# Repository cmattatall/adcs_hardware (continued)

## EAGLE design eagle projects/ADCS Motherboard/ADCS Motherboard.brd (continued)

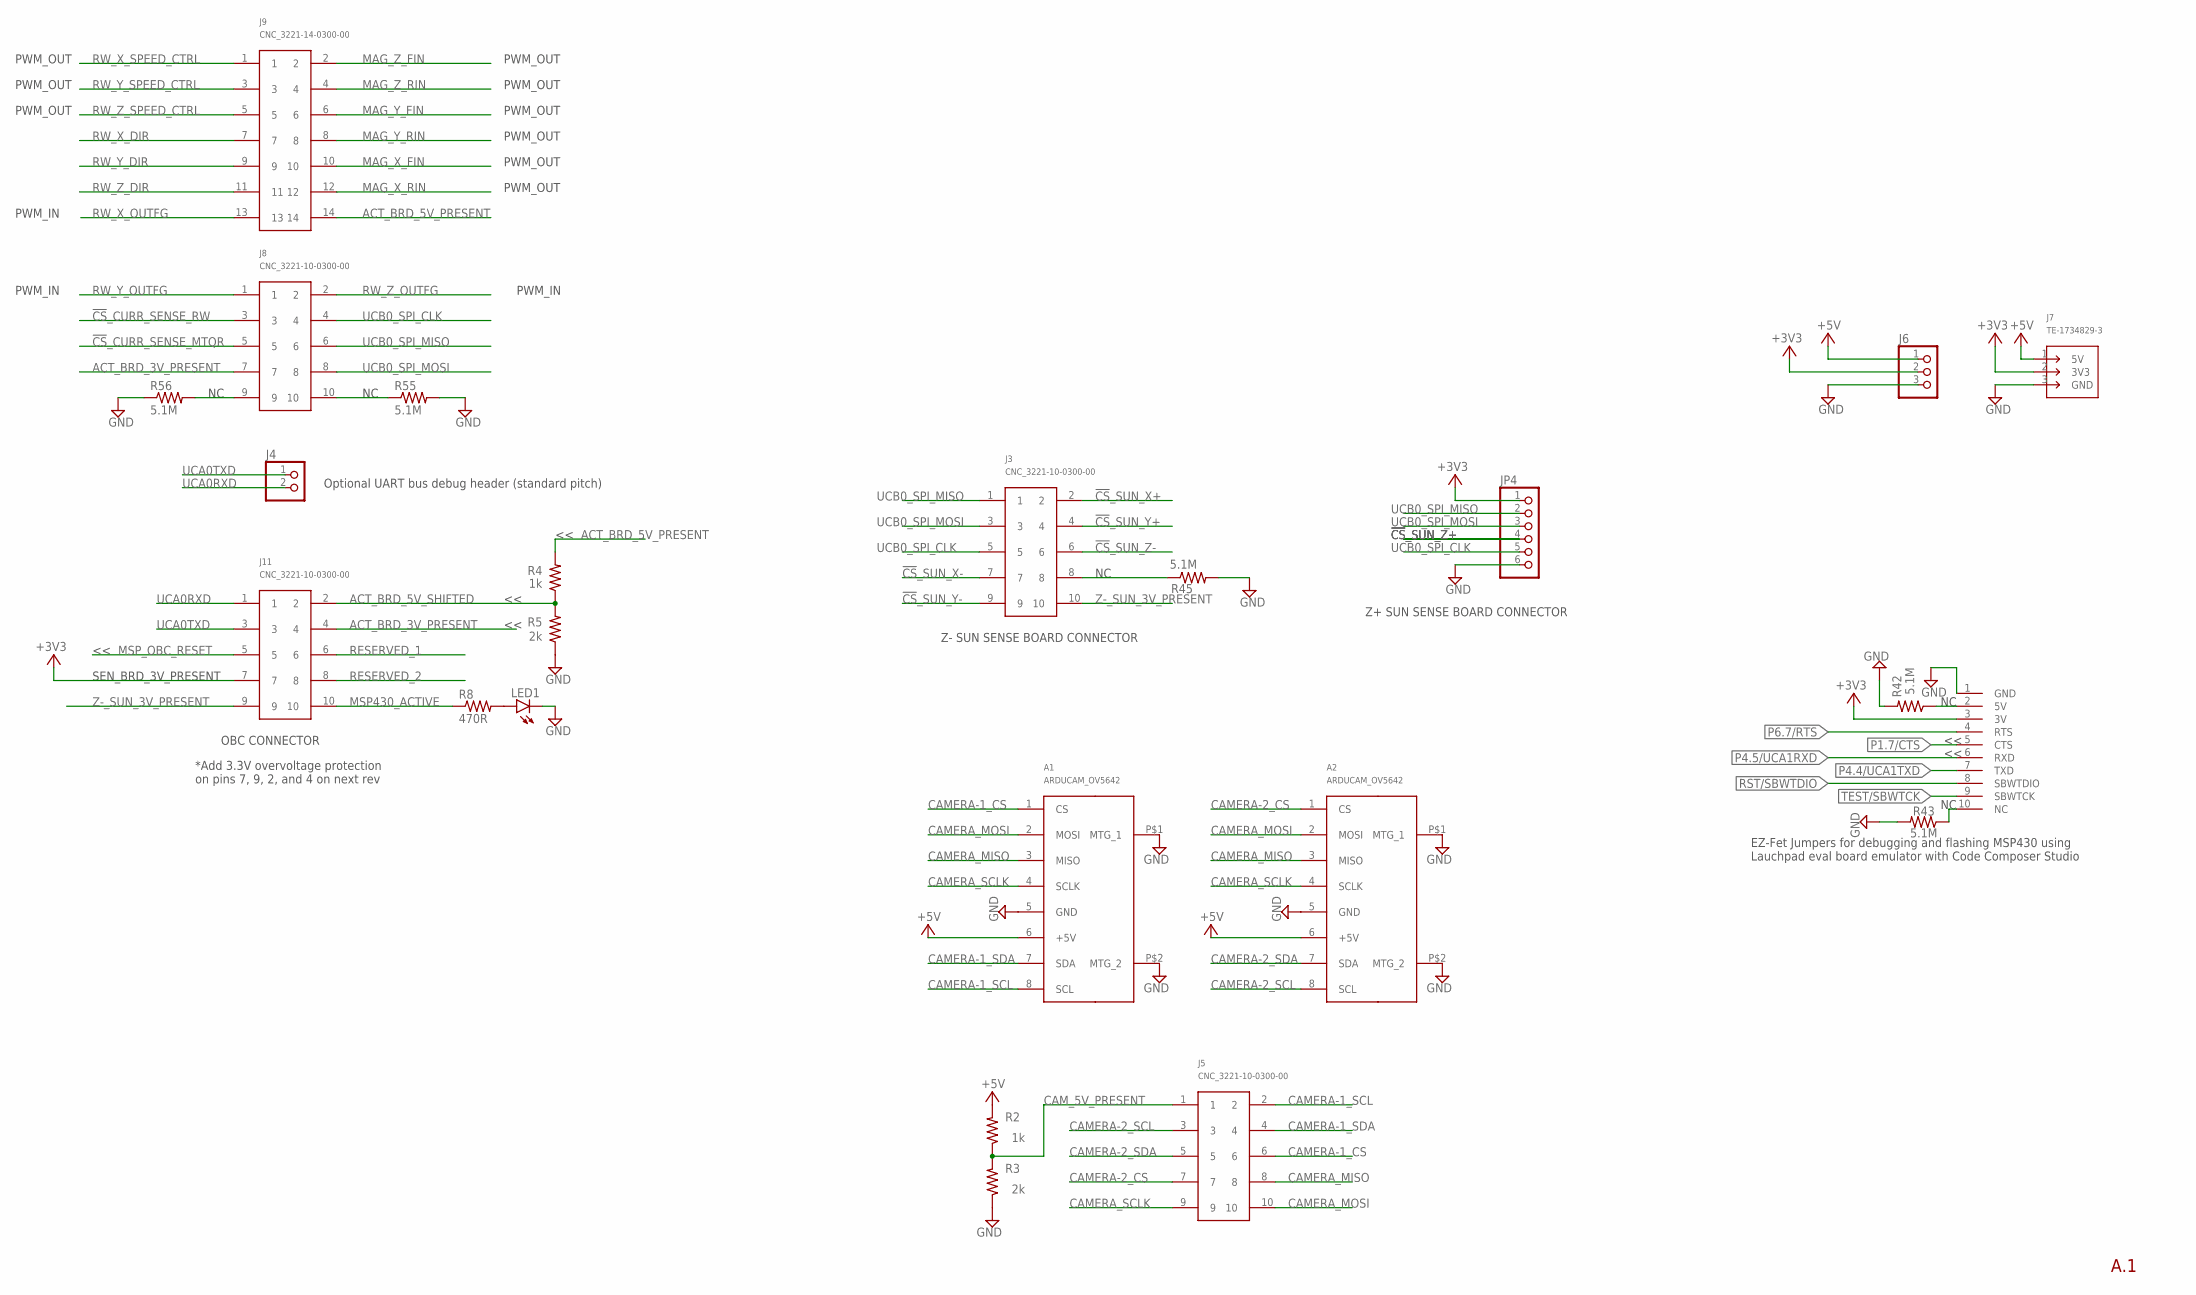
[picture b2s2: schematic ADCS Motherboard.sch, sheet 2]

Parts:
A1, A2: ARDUCAM_OV5642; ARDUCAM
J1: HDR_10_EZFET_DEBUGGER; HDRV10W66P254_10X1_2540X254H858
J3, J5, J8, J11: CNC_3221-10-0300-00
J4: HDR_1X2_; 1X02
J6: PINHD-1X3; 1X03
J7: TE-1734829-3
J9: CNC_3221-14-0300-00
JP4: PINHD-1X6; 1X06
LED1: LEDCHIP-LED0603; CHIP-LED0603
R2, R4: 1k; R0603
R3, R5: 2k; R0603
R8: 470R; R0603
R42, R43, R45: 5.1M; R0402
R55, R56: 5.1M; R0603

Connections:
!CS!_CURR_SENSE_MTQR: J8.5; also elsewhere on the board
!CS!_CURR_SENSE_RW: J8.3; also elsewhere on the board
!CS!_SUN_X+: J3.2; also elsewhere on the board
!CS!_SUN_X-: J3.7; also elsewhere on the board
!CS!_SUN_Y+: J3.4; also elsewhere on the board
!CS!_SUN_Y-: J3.9; also elsewhere on the board
!CS!_SUN_Z+: JP4.4; also elsewhere on the board
!CS!_SUN_Z-: J3.6; also elsewhere on the board
+3V3: J1.3 (3V), J6.2, J7.2 (3V3), J11.7, JP4.1; also elsewhere on the board
+5V: A1.6 (+5V), A2.6 (+5V), J6.1, J7.1 (5V), R2.2; also elsewhere on the board
ACT_BRD_3V_PRESENT: J8.7, J11.4
ACT_BRD_5V_PRESENT: J9.14, R4.2
ACT_BRD_5V_SHIFTED: J11.2, R4.1, R5.2
CAMERA-1_CS: A1.1 (CS), J5.6
CAMERA-1_SCL: A1.8 (SCL), J5.2
CAMERA-1_SDA: A1.7 (SDA), J5.4
CAMERA-2_CS: A2.1 (CS), J5.7
CAMERA-2_SCL: A2.8 (SCL), J5.3
CAMERA-2_SDA: A2.7 (SDA), J5.5
CAMERA_MISO: A1.3 (MISO), A2.3 (MISO), J5.8
CAMERA_MOSI: A1.2 (MOSI), A2.2 (MOSI), J5.10
CAMERA_SCLK: A1.4 (SCLK), A2.4 (SCLK), J5.9
CAM_5V_PRESENT: J5.1, R2.1, R3.2
GND: A1.5 (GND), A1.P$1 (MTG_1), A1.P$2 (MTG_2), A2.5 (GND), A2.P$1 (MTG_1), A2.P$2 (MTG_2), J1.1 (GND), J6.3, J7.3 (GND), JP4.6, LED1.C, R3.1, R5.1, R42.2, R43.2, R45.2, R55.2, R56.1; also elsewhere on the board
MAG_X_FIN: J9.10; also elsewhere on the board
MAG_X_RIN: J9.12; also elsewhere on the board
MAG_Y_FIN: J9.6; also elsewhere on the board
MAG_Y_RIN: J9.8; also elsewhere on the board
MAG_Z_FIN: J9.2; also elsewhere on the board
MAG_Z_RIN: J9.4; also elsewhere on the board
MSP430_ACTIVE: J11.10, R8.1; also elsewhere on the board
MSP_OBC_RESET: J11.5; also elsewhere on the board
unnamed: LED1.A, R8.2
unnamed: J1.2 (5V), R42.1
unnamed: J1.10 (NC), R43.1
unnamed: J8.9, R56.2
unnamed: J8.10, R55.1
unnamed: J3.8, R45.1
P1.7/CTS: J1.5 (CTS); also elsewhere on the board
P4.4/UCA1TXD: J1.7 (TXD); also elsewhere on the board
P4.5/UCA1RXD: J1.6 (RXD); also elsewhere on the board
P6.7/RTS: J1.4 (RTS); also elsewhere on the board
RESERVED_1: J11.6; also elsewhere on the board
RESERVED_2: J11.8; also elsewhere on the board
RST/SBWTDIO: J1.8 (SBWTDIO); also elsewhere on the board
RW_X_DIR: J9.7; also elsewhere on the board
RW_X_OUTFG: J9.13; also elsewhere on the board
RW_X_SPEED_CTRL: J9.1; also elsewhere on the board
RW_Y_DIR: J9.9; also elsewhere on the board
RW_Y_OUTFG: J8.1; also elsewhere on the board
RW_Y_SPEED_CTRL: J9.3; also elsewhere on the board
RW_Z_DIR: J9.11; also elsewhere on the board
RW_Z_OUTFG: J8.2; also elsewhere on the board
RW_Z_SPEED_CTRL: J9.5; also elsewhere on the board
TEST/SBWTCK: J1.9 (SBWTCK); also elsewhere on the board
UCA0RXD: J4.2, J11.1; also elsewhere on the board
UCA0TXD: J4.1, J11.3; also elsewhere on the board
UCB0_SPI_CLK: J3.5, J8.4, JP4.5; also elsewhere on the board
UCB0_SPI_MISO: J3.1, J8.6, JP4.2; also elsewhere on the board
UCB0_SPI_MOSI: J3.3, J8.8, JP4.3; also elsewhere on the board
Z-_SUN_3V_PRESENT: J3.10, J11.9

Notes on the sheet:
PWM_OUT
OBC CONNECTOR
SEN_BRD_3V_PRESENT
*Add 3.3V overvoltage protection on pins 7, 9, 2, and 4 on next rev
EZ-Fet Jumpers for debugging and flashing MSP430 using Lauchpad eval board emulator with Code Composer Studio
Optional UART bus debug header (standard pitch)
A.1
Z- SUN SENSE BOARD CONNECTOR
Z+ SUN SENSE BOARD CONNECTOR
PWM_IN

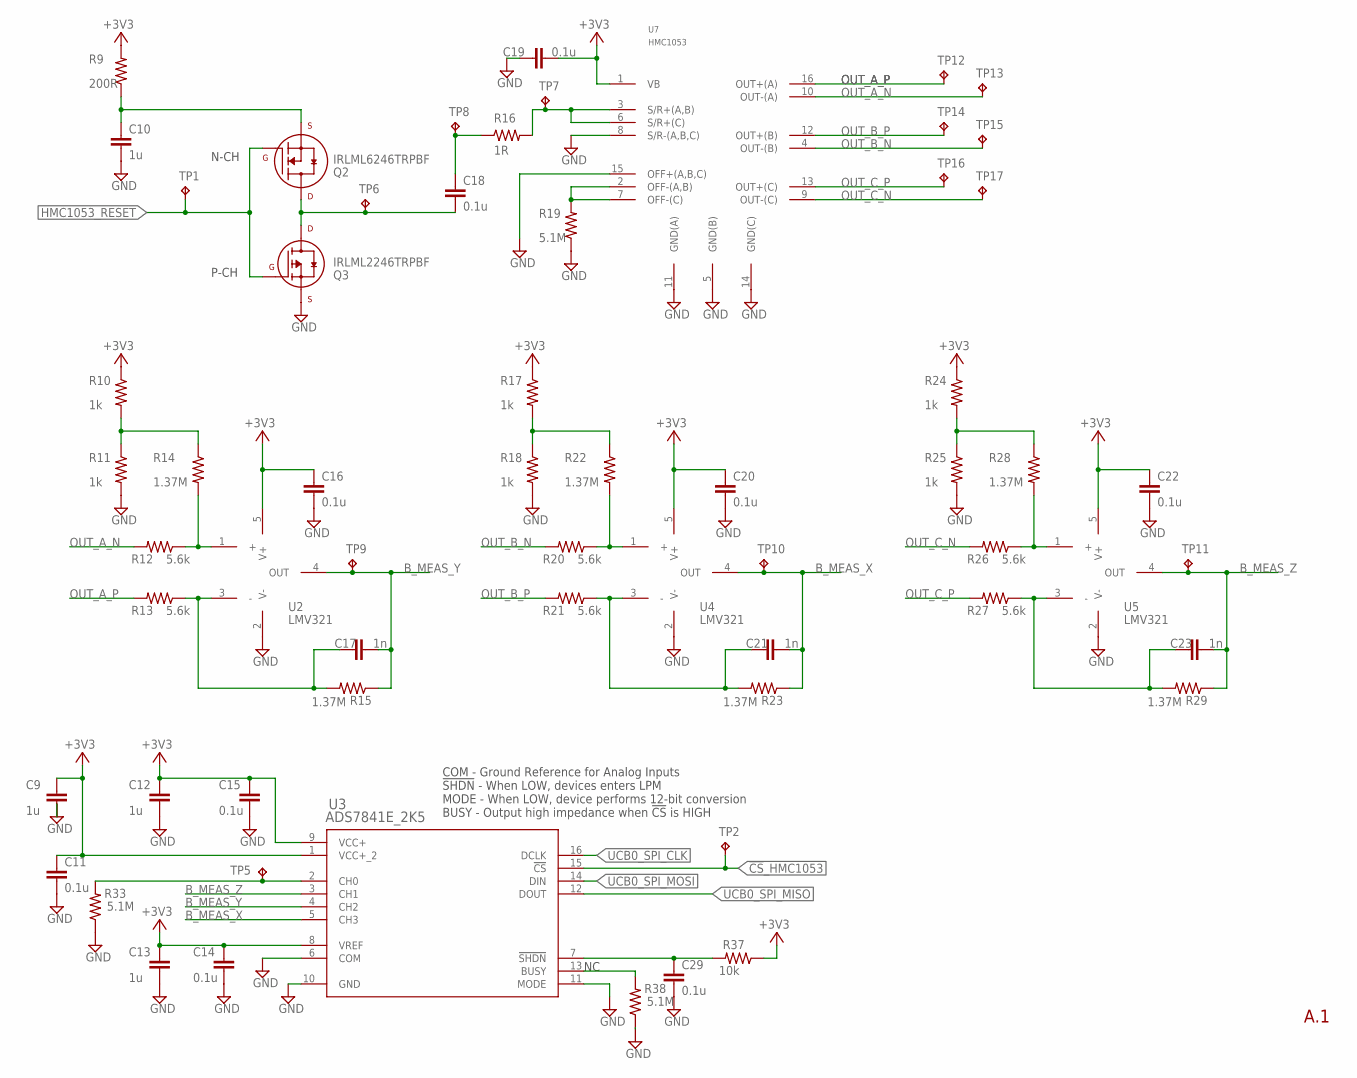
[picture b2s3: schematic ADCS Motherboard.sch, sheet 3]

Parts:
C9, C12, C13: 1u; C0805
C10: 1u; C0603
C11, C14, C15, C16, C19, C20, C22, C29: 0.1u; C0603
C17, C21, C23: 1n; C0603
C18: 0.1u; C0805
Q2: IRLML6246TRPBF; SOT23-3P95_237X112L25X40N_MICRO3
Q3: IRLML2246TRPBF; SOT23-3P95_237X112L25X40N_MICRO3
R9: 200R; R0805
R10, R11, R17, R18, R24, R25: 1k; R0603
R12, R13, R20, R21, R26, R27: 5.6k; R0603
R14, R15, R22, R23, R28, R29: 1.37M; R0603
R16: 1R; R0805
R19: 5.1M; R0805
R33, R38: 5.1M; R0402
R37: 10k; R0805
TP1, TP2, TP5, TP6, TP7, TP8, TP9, TP10, TP11, TP12, TP13, TP14, TP15, TP16, TP17: TESTPOINT; TP_P76H50
U2, U4, U5: LMV321; SC70-5P65_210X110L36X22N
U3: ADS7841E_2K5; DBQ16
U7: HMC1053; LCCS16P127_736X736X279L127X50N

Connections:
!CS!_HMC1053: TP2.1, U3.15 (!CS); also elsewhere on the board
+3V3: C9.1, C11.1, C12.1, C13.1, C14.1, C15.1, C16.1, C19.1, C20.1, C22.1, R9.2, R10.1, R17.1, R24.1, R37.1, U2.5 (V+), U3.1 (VCC+_2), U3.8 (VREF), U3.9 (VCC+), U4.5 (V+), U5.5 (V+), U7.1 (VB); also elsewhere on the board
B_MEAS_X: C21.2, R23.1, TP10.1, U3.5 (CH3), U4.4 (OUT)
B_MEAS_Y: C17.2, R15.1, TP9.1, U2.4 (OUT), U3.4 (CH2)
B_MEAS_Z: C23.2, R29.1, TP11.1, U3.3 (CH1), U5.4 (OUT)
GND: C9.2, C10.1, C11.2, C12.2, C13.2, C14.2, C15.2, C16.2, C19.2, C20.2, C22.2, C29.2, Q3.2 (S), R11.2, R18.2, R19.1, R25.2, R33.1, R38.1, U2.2 (V-), U3.6 (COM), U3.10 (GND), U3.11 (MODE), U4.2 (V-), U5.2 (V-), U7.5 (GND(B)), U7.8 (S/R-(A,B,C)), U7.11 (GND(A)), U7.14 (GND(C)), U7.15 (OFF+(A,B,C)); also elsewhere on the board
HMC1053_RESET: Q2.1 (G), Q3.1 (G), TP1.1; also elsewhere on the board
unnamed: C18.1, Q2.3 (D), Q3.3 (D), TP6.1
unnamed: R10.2, R11.1, R14.1
unnamed: C17.1, R13.1, R15.2, U2.3 (-)
unnamed: R12.1, R14.2, U2.1 (+)
unnamed: R33.2, TP5.1, U3.2 (CH0)
unnamed: R38.2, U3.13 (BUSY)
unnamed: C29.1, R37.2, U3.7 (!SHDN)
unnamed: C18.2, R16.1, TP8.1
unnamed: R19.2, U7.2 (OFF-(A,B)), U7.7 (OFF-(C))
unnamed: R16.2, TP7.1, U7.3 (S/R+(A,B)), U7.6 (S/R+(C))
unnamed: C10.2, Q2.2 (S), R9.1
unnamed: R17.2, R18.1, R22.1
unnamed: C21.1, R21.1, R23.2, U4.3 (-)
unnamed: R20.1, R22.2, U4.1 (+)
unnamed: R24.2, R25.1, R28.1
unnamed: C23.1, R27.1, R29.2, U5.3 (-)
unnamed: R26.1, R28.2, U5.1 (+)
OUT_A_N: R12.2, TP13.1, U7.10 (OUT-(A))
OUT_A_P: R13.2, TP12.1, U7.16 (OUT+(A))
OUT_B_N: R20.2, TP15.1, U7.4 (OUT-(B))
OUT_B_P: R21.2, TP14.1, U7.12 (OUT+(B))
OUT_C_N: R26.2, TP17.1, U7.9 (OUT-(C))
OUT_C_P: R27.2, TP16.1, U7.13 (OUT+(C))
UCB0_SPI_CLK: U3.16 (DCLK); also elsewhere on the board
UCB0_SPI_MISO: U3.12 (DOUT); also elsewhere on the board
UCB0_SPI_MOSI: U3.14 (DIN); also elsewhere on the board

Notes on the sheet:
COM - Ground Reference for Analog Inputs !SHDN! - When LOW, devices enters LPM MODE - When LOW, device performs 12-bit conversion BUSY - Output high impedance when !CS! is HIGH
P-CH
N-CH
A.1

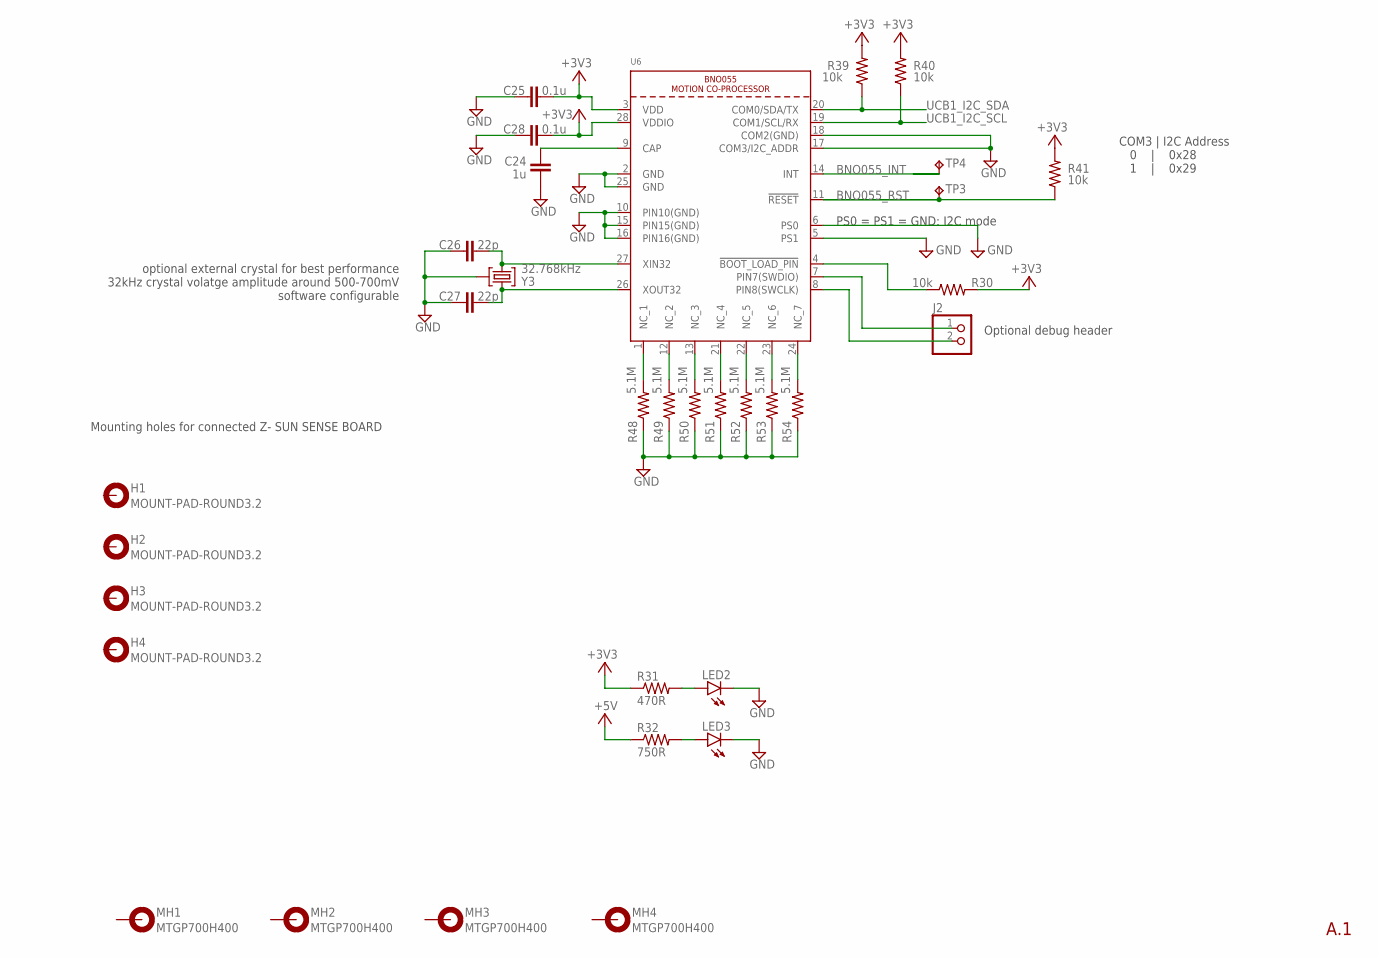
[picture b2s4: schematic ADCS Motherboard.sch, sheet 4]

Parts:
C24: 1u; C0402
C25, C28: 0.1u; C0402
C26, C27: 22p; C0402
H1, H2, H3, H4: MOUNT-PAD-ROUND3.2; 3,2-PAD
J2: HDR_1X2_; 1X02
LED2, LED3: LEDCHIP-LED0603; CHIP-LED0603
MH1, MH2, MH3, MH4: MTGP700H400
R30, R39, R40, R41: 10k; R0402
R31: 470R; R0603
R32: 750R; R0603
R48, R49, R50, R51, R52, R53, R54: 5.1M; R0402
TP3, TP4: TESTPOINT; TP_P76H50
U6: BNO055
Y3: 32.768kHz; MS3V-T1R

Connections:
+3V3: C25.2, C28.2, R30.2, R31.1, R39.2, R40.2, R41.2, U6.3 (VDD), U6.28 (VDDIO); also elsewhere on the board
+5V: R32.1; also elsewhere on the board
BNO055_INT: TP4.1, U6.14 (INT); also elsewhere on the board
BNO055_RST: R41.1, TP3.1, U6.11 (!RESET); also elsewhere on the board
GND: C24.1, C25.1, C26.1, C27.1, C28.1, LED2.C, LED3.C, R48.1, R49.1, R50.1, R51.1, R52.1, R53.1, R54.1, U6.2 (GND), U6.5 (PS1), U6.6 (PS0), U6.10 (PIN10(GND)), U6.15 (PIN15(GND)), U6.16 (PIN16(GND)), U6.17 (COM3/I2C_ADDR), U6.18 (COM2(GND)), U6.25 (GND), Y3.P3 (GND); also elsewhere on the board
unnamed: LED2.A, R31.2
unnamed: LED3.A, R32.2
unnamed: R30.1, U6.4 (!BOOT_LOAD_PIN)
unnamed: C24.2, U6.9 (CAP)
unnamed: C26.2, U6.27 (XIN32), Y3.P1 (1)
unnamed: C27.2, U6.26 (XOUT32), Y3.P2 (2)
unnamed: J2.1, U6.7 (PIN7(SWDIO))
unnamed: J2.2, U6.8 (PIN8(SWCLK))
unnamed: R48.2, U6.1 (NC_1)
unnamed: R49.2, U6.12 (NC_2)
unnamed: R50.2, U6.13 (NC_3)
unnamed: R51.2, U6.21 (NC_4)
unnamed: R52.2, U6.22 (NC_5)
unnamed: R53.2, U6.23 (NC_6)
unnamed: R54.2, U6.24 (NC_7)
UCB1_I2C_SCL: R40.1, U6.19 (COM1/SCL/RX); also elsewhere on the board
UCB1_I2C_SDA: R39.1, U6.20 (COM0/SDA/TX); also elsewhere on the board

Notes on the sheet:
optional external crystal for best performance 32kHz crystal volatge amplitude around 500-700mV software configurable
Optional debug header
PS0 = PS1 = GND: I2C mode
COM3 | I2C Address 0 | 0x28 1 | 0x29
Mounting holes for connected Z- SUN SENSE BOARD
A.1

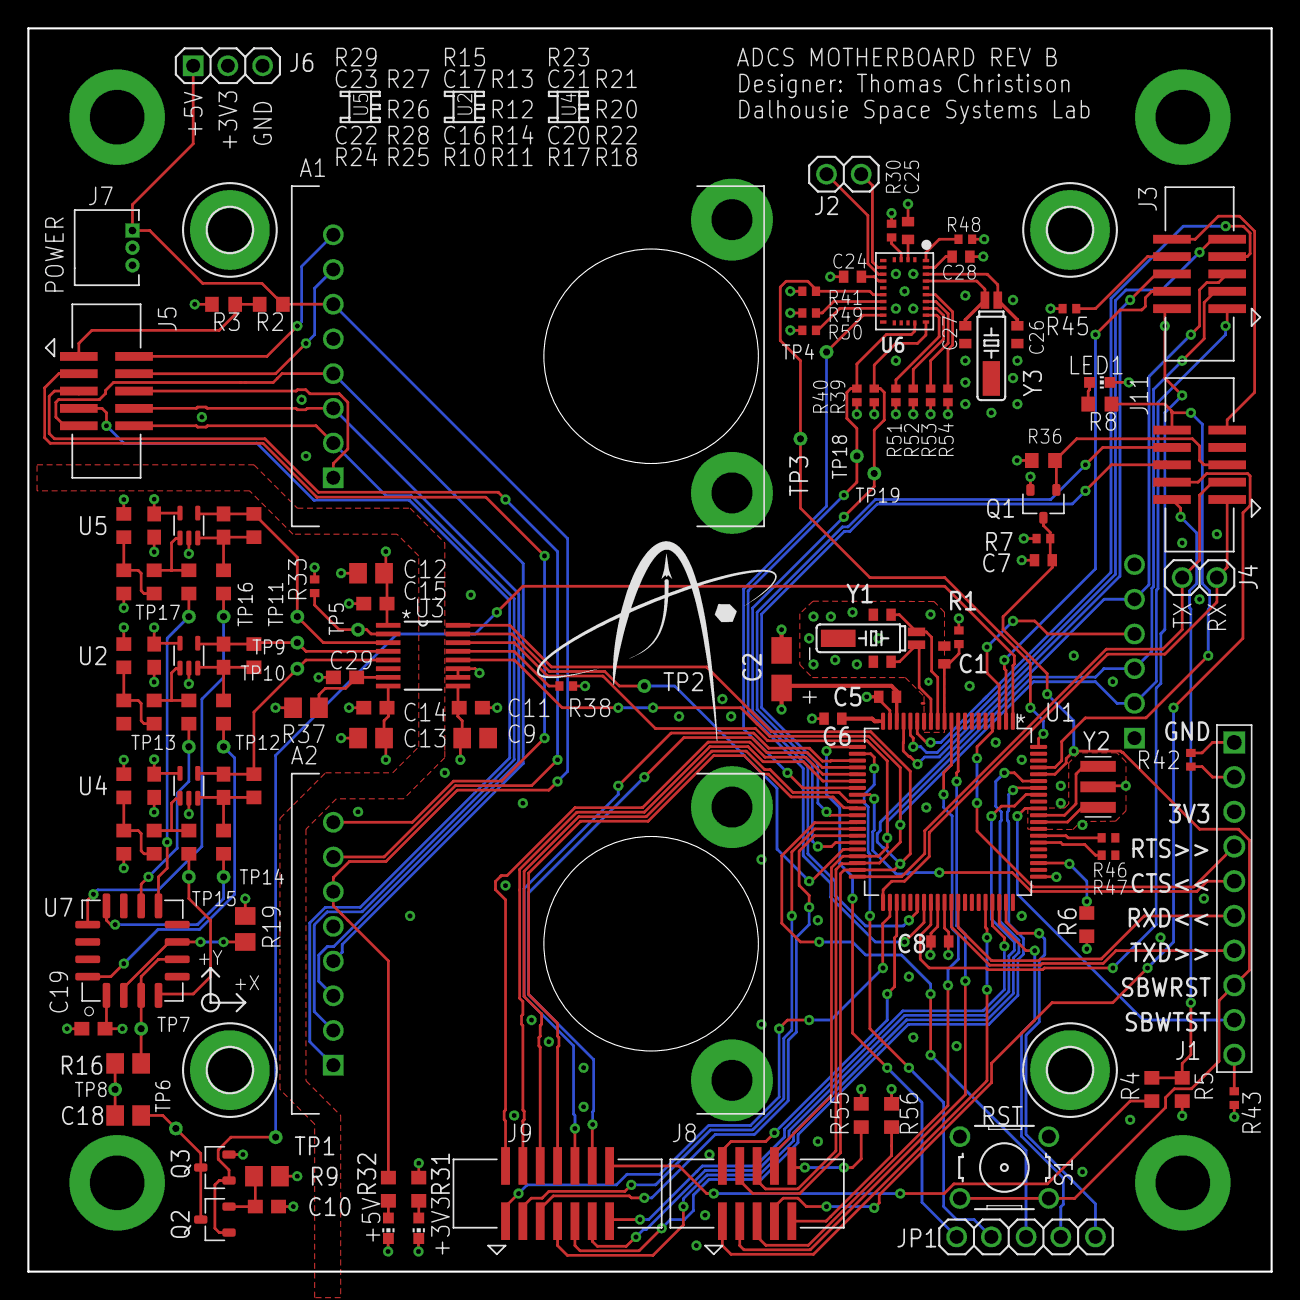
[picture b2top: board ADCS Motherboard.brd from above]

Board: 4 copper layers, 91.0 x 91.0 mm, 140 parts (1 on the bottom side), 122 nets.

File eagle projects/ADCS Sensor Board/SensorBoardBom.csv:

"Part";"Value";"Device";"Package";"Description";"";
"A1";"HMC1053PA0242";"HMC1053PA0242";"PA0242";"";"";
"A2";"ARDUCAM_OV5642";"ARDUCAM_OV5642";"ARDUCAM";"";"";
"A3";"ARDUCAM_OV5642";"ARDUCAM_OV5642";"ARDUCAM";"";"";
"C1";"100n";"C-EUC0402";"C0402";"CAPACITOR, European symbol";"";
"C2";"10u";"POLARIZED_CAP";"A/3216-18R";"";"";
"C3";"12p";"C-EUC0402";"C0402";"CAPACITOR, European symbol";"";
"C4";"12p";"C-EUC0402";"C0402";"CAPACITOR, European symbol";"";
"C5";"100n";"C-EUC0402";"C0402";"CAPACITOR, European symbol";"";
"C6";"470n";"C-EUC0402";"C0402";"CAPACITOR, European symbol";"";
"C7";"1n";"C-EUC0402";"C0402";"CAPACITOR, European symbol";"";
"C8";"100n";"C-EUC0402";"C0402";"CAPACITOR, European symbol";"";
"C9";"1u";"C-EUC1206";"C1206";"CAPACITOR, European symbol";"";
"C10";"0.1u";"C-EUC0603";"C0603";"CAPACITOR, European symbol";"";
"C11";"0.1u";"C-EUC0603";"C0603";"CAPACITOR, European symbol";"";
"C12";"1u";"C-EUC1206";"C1206";"CAPACITOR, European symbol";"";
"C13";"1u";"C-EUC1206";"C1206";"CAPACITOR, European symbol";"";
"C14";"0.1u";"C-EUC0603";"C0603";"CAPACITOR, European symbol";"";
"C15";"0.1u";"C-EUC0603";"C0603";"CAPACITOR, European symbol";"";
"C16";"0.1u";"C-EUC0603";"C0603";"CAPACITOR, European symbol";"";
"C17";"1n";"C-EUC0805";"C0805";"CAPACITOR, European symbol";"";
"C18";"1n";"C-EUC1206";"C1206";"CAPACITOR, European symbol";"";
"C19";"0.1u";"C-EUC0603";"C0603";"CAPACITOR, European symbol";"";
"C20";"0.1u";"C-EUC0603";"C0603";"CAPACITOR, European symbol";"";
"C21";"1n";"C-EUC0805";"C0805";"CAPACITOR, European symbol";"";
"C22";"0.1u";"C-EUC0603";"C0603";"CAPACITOR, European symbol";"";
"C23";"1n";"C-EUC0805";"C0805";"CAPACITOR, European symbol";"";
"C24";"470n";"C-EUC0805";"C0805";"CAPACITOR, European symbol";"";
"J1";"HDR_10_EZFET_DEBUGGER";"HDR_10_EZFET_DEBUGGER";"HDRV10W66P254_10X1_2540X254H858";"";"";
"J2";"MTI-1_8428-11B1-RK-TP";"MTI-1_8428-11B1-RK-TP";"PLCC-28_SOCKET_TH";"";"";
"JP1";"";"PINHD-1X4";"1X04";"PIN HEADER";"";
"JP2";"";"PINHD-2X8";"2X08";"PIN HEADER";"";
"JP3";"";"PINHD-2X8";"2X08";"PIN HEADER";"";
"JP4";"";"PINHD-1X4";"1X04";"PIN HEADER";"";
"JP5";"";"PINHD-2X6";"2X06";"PIN HEADER";"";
"JP6";"";"JP1Q_";"1X02";"JUMPER";"";
"JP7";"";"PINHD-1X7";"1X07";"PIN HEADER";"";
"JP8";"";"PINHD-1X4";"1X04";"PIN HEADER";"";
"JP9";"";"PINHD-1X3";"1X03";"PIN HEADER";"";
"LED1";"";"LEDCHIP-LED0603";"CHIP-LED0603";"LED";"";
"LED2";"";"LEDCHIP-LED0603";"CHIP-LED0603";"LED";"";
"LED3";"";"LEDCHIP-LED0603";"CHIP-LED0603";"LED";"";
"MH1";"MTGP700H400";"MTGP700H400";"MTGP700H400";"";"";
"MH2";"MTGP700H400";"MTGP700H400";"MTGP700H400";"";"";
"MH3";"MTGP700H400";"MTGP700H400";"MTGP700H400";"";"";
"MH4";"MTGP700H400";"MTGP700H400";"MTGP700H400";"";"";
"Q1";"BC850SMD";"BC850SMD";"SOT23-BEC";"NPN Transistor";"";
"Q2";"IRF7507TRPBF";"IRF7507TRPBF";"SOP8P65_300X490X111L53X30N";"";"";
"R1";"0R";"R-US_R0402";"R0402";"RESISTOR, American symbol";"";
"R2";"1k";"R-US_R0402";"R0402";"RESISTOR, American symbol";"";
"R3";"2k";"R-US_R0402";"R0402";"RESISTOR, American symbol";"";
"R4";"1k";"R-US_R0402";"R0402";"RESISTOR, American symbol";"";
"R5";"2k";"R-US_R0402";"R0402";"RESISTOR, American symbol";"";
"R6";"1M";"R-US_R0402";"R0402";"RESISTOR, American symbol";"";
"R7";"47k";"R-US_R0402";"R0402";"RESISTOR, American symbol";"";
"R8";"470R";"R-US_R0603";"R0603";"RESISTOR, American symbol";"";
"R9";"200R";"R-US_R1206";"R1206";"RESISTOR, American symbol";"";
"R10";"1k";"R-US_R0805";"R0805";"RESISTOR, American symbol";"";
"R11";"1k";"R-US_R0805";"R0805";"RESISTOR, American symbol";"";
"R12";"5.6k";"R-US_R0805";"R0805";"RESISTOR, American symbol";"";
"R13";"5.6k";"R-US_R0805";"R0805";"RESISTOR, American symbol";"";
"R14";"1.37M";"R-US_R0805";"R0805";"RESISTOR, American symbol";"";
"R15";"1.37M";"R-US_R0805";"R0805";"RESISTOR, American symbol";"";
"R16";"0R";"R-US_R0805";"R0805";"RESISTOR, American symbol";"";
"R17";"1k";"R-US_R0805";"R0805";"RESISTOR, American symbol";"";
"R18";"1k";"R-US_R0805";"R0805";"RESISTOR, American symbol";"";
"R19";"5.1M";"R-US_R1206";"R1206";"RESISTOR, American symbol";"";
"R20";"5.6k";"R-US_R0805";"R0805";"RESISTOR, American symbol";"";
"R21";"5.6k";"R-US_R0805";"R0805";"RESISTOR, American symbol";"";
"R22";"1.37M";"R-US_R0805";"R0805";"RESISTOR, American symbol";"";
"R23";"1.37M";"R-US_R0805";"R0805";"RESISTOR, American symbol";"";
"R24";"1k";"R-US_R0805";"R0805";"RESISTOR, American symbol";"";
"R25";"1k";"R-US_R0805";"R0805";"RESISTOR, American symbol";"";
"R26";"5.6k";"R-US_R0805";"R0805";"RESISTOR, American symbol";"";
"R27";"5.6k";"R-US_R0805";"R0805";"RESISTOR, American symbol";"";
"R28";"1.37M";"R-US_R0805";"R0805";"RESISTOR, American symbol";"";
"R29";"1.37M";"R-US_R0805";"R0805";"RESISTOR, American symbol";"";
"R30";"27R";"R-US_R0805";"R0805";"RESISTOR, American symbol";"";
"R31";"470R";"R-US_R0603";"R0603";"RESISTOR, American symbol";"";
"R32";"750R";"R-US_R0603";"R0603";"RESISTOR, American symbol";"";
"R33";"0R";"R-US_R0805";"R0805";"RESISTOR, American symbol";"";
"R34";"0R";"R-US_R0805";"R0805";"RESISTOR, American symbol";"";
"R35";"0R";"R-US_R0805";"R0805";"RESISTOR, American symbol";"";
"S1";"RST";"10-XX";"B3F-10XX";"OMRON SWITCH";"";
"TP1";"TESTPOINT";"TESTPOINT";"TP_P76H50";"";"";
"TP2";"TESTPOINT";"TESTPOINT";"TP_P76H50";"";"";
"TP3";"TESTPOINT";"TESTPOINT";"TP_P76H50";"";"";
"TP4";"TESTPOINT";"TESTPOINT";"TP_P76H50";"";"";
"TP5";"TESTPOINT";"TESTPOINT";"TP_P76H50";"";"";
"U1";"MSP430F5529IPN";"MSP430F5529IPN";"QFP80P50_1400X1400X160L60X22N";"";"";
"U2";"LMV321";"LMV321";"SOT23-5P65_210X110L36X22N";"";"";
"U3";"ADS7841E_2K5";"ADS7841E_2K5";"DBQ16";"";"";
"U4";"LMV321";"LMV321";"SOT23-5P65_210X110L36X22N";"";"";
"U5";"LMV321";"LMV321";"SOT23-5P65_210X110L36X22N";"";"";
"Y1";"32.768kHz";"MS3V-T1R";"MS3V-T1R";"";"";
"Y2";"CSTCR4M00G15L99";"CSTCR4M00G15L996M00G53Z";"MURATA-FILTER_CSTCR";"";"";

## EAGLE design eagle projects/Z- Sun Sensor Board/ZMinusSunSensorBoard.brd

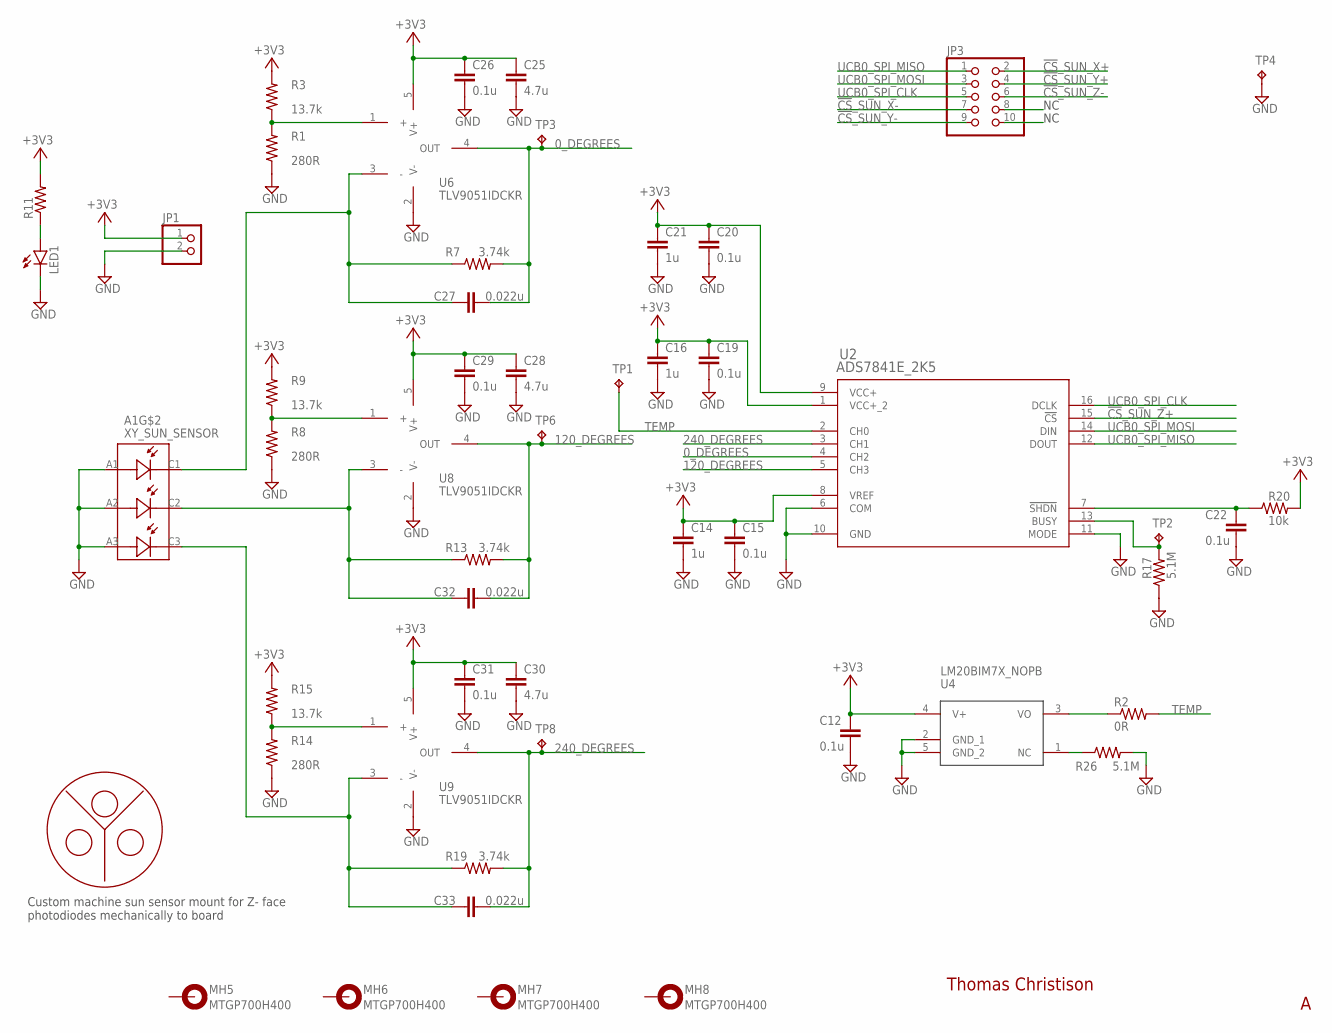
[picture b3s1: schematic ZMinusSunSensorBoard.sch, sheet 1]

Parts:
A1: XY_SUN_SENSOR; XY_SUN_SENOR_MASK
C12, C15, C19, C20, C22, C26, C29, C31: 0.1u; C0402
C14, C16, C21: 1u; C0402
C25, C28, C30: 4.7u; C0805
C27, C32, C33: 0.022u; C0402
JP1: PINHD-1X2; 1X02
JP3: PINHD-2X5; 2X05
LED1: LEDCHIP-LED0603; CHIP-LED0603
MH5, MH6, MH7, MH8: MTGP700H400
R1, R8, R14: 280R; R0402
R2: 0R; R0805
R3, R9, R15: 13.7k; R0402
R7, R13, R19: 3.74k; R0402
R11: R-US_R0603; R0603
R17, R26: 5.1M; R0402
R20: 10k; R0402
TP1, TP2, TP3, TP4, TP6, TP8: TESTPOINT; TP_P76H50
U2: ADS7841E_2K5; DBQ16
U4: LM20BIM7X_NOPB; SOT23-5P65_210X110L40X22N_LM20
U6, U8, U9: TLV9051IDCKR; SC70-5P65_210X110L36X22N_TLV9051

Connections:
0_DEGREES: C27.2, R7.2, TP3.1, U2.4 (CH2), U6.4 (OUT)
120_DEGREES: C32.2, R13.2, TP6.1, U2.5 (CH3), U8.4 (OUT)
240_DEGREES: C33.2, R19.2, TP8.1, U2.3 (CH1), U9.4 (OUT)
!CS!_SUN_X+: JP3.2; also elsewhere on the board
!CS!_SUN_X-: JP3.7; also elsewhere on the board
!CS!_SUN_Y+: JP3.4; also elsewhere on the board
!CS!_SUN_Y-: JP3.9; also elsewhere on the board
!CS!_SUN_Z+: U2.15 (!CS)
!CS!_SUN_Z-: JP3.6
+3V3: C12.1, C14.1, C15.1, C16.1, C19.1, C20.1, C21.1, C25.1, C26.1, C28.1, C29.1, C30.1, C31.1, JP1.1, R3.2, R9.2, R11.2, R15.2, R20.2, U2.1 (VCC+_2), U2.8 (VREF), U2.9 (VCC+), U4.4 (V+), U6.5 (V+), U8.5 (V+), U9.5 (V+); also elsewhere on the board
GND: A1.A1, A1.A2, A1.A3, C12.2, C14.2, C15.2, C16.2, C19.2, C20.2, C21.2, C22.2, C25.2, C26.2, C28.2, C29.2, C30.2, C31.2, JP1.2, LED1.C, R1.1, R8.1, R14.1, R17.1, R26.2, TP4.1, U2.6 (COM), U2.10 (GND), U2.11 (MODE), U4.2 (GND_1), U4.5 (GND_2), U6.2 (V-), U8.2 (V-), U9.2 (V-); also elsewhere on the board
unnamed: R2.1, U4.3 (VO)
unnamed: R17.2, TP2.1, U2.13 (BUSY)
unnamed: A1.C1, C27.1, R7.1, U6.3 (-)
unnamed: R1.2, R3.1, U6.1 (+)
unnamed: R26.1, U4.1 (NC)
unnamed: A1.C2, C32.1, R13.1, U8.3 (-)
unnamed: R8.2, R9.1, U8.1 (+)
unnamed: A1.C3, C33.1, R19.1, U9.3 (-)
unnamed: R14.2, R15.1, U9.1 (+)
unnamed: C22.1, R20.1, U2.7 (!SHDN)
unnamed: LED1.A, R11.1
TEMP: R2.2, TP1.1, U2.2 (CH0)
UCB0_SPI_CLK: JP3.5, U2.16 (DCLK); also elsewhere on the board
UCB0_SPI_MISO: JP3.1, U2.12 (DOUT); also elsewhere on the board
UCB0_SPI_MOSI: JP3.3, U2.14 (DIN); also elsewhere on the board

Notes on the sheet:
Custom machine sun sensor mount for Z- face photodiodes mechanically to board
Thomas Christison

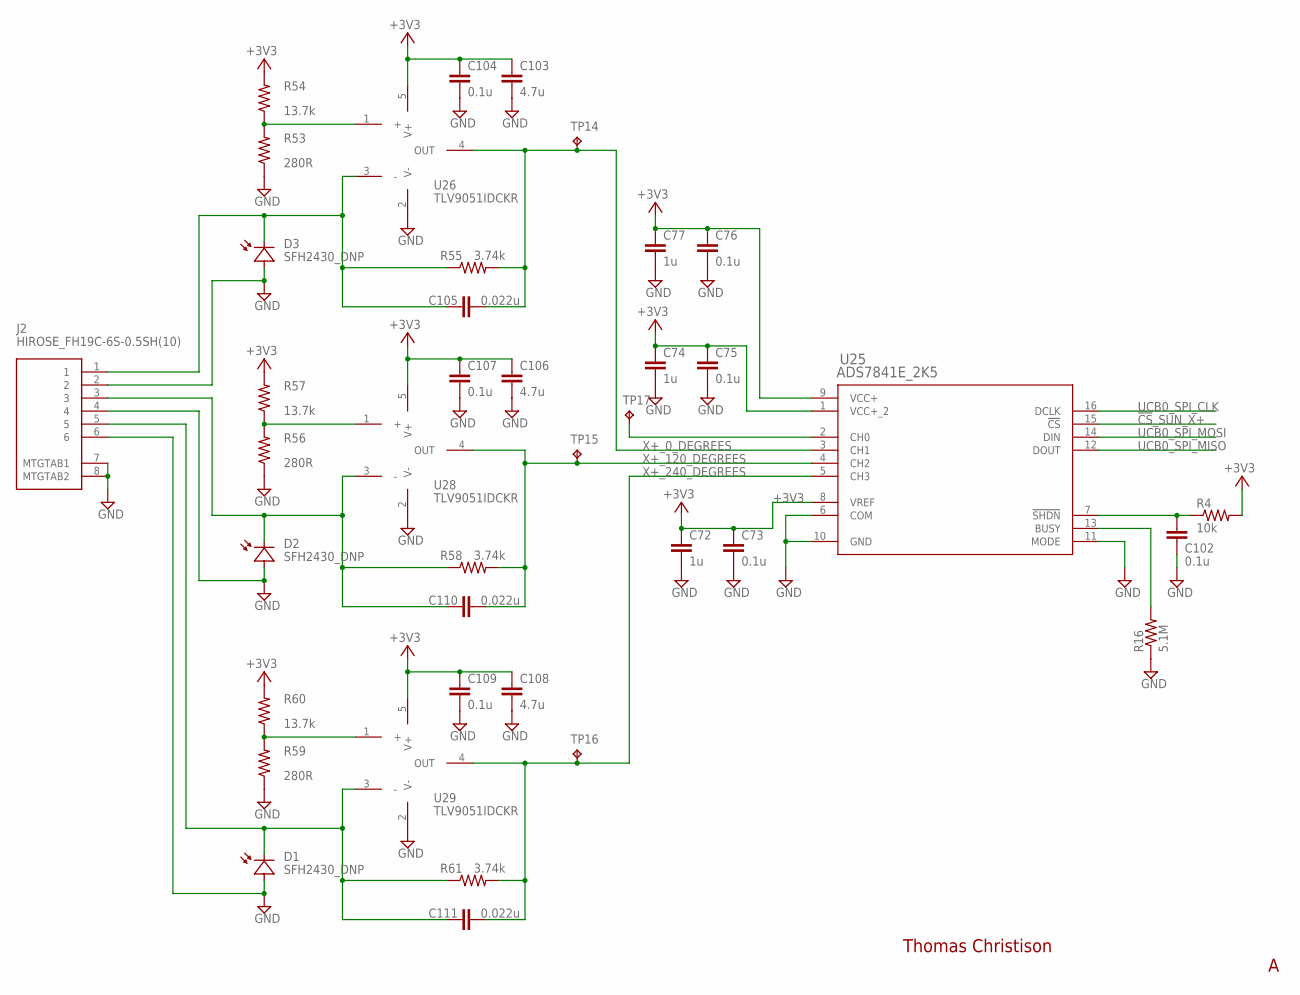
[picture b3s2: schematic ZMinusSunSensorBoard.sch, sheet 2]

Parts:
C72, C74, C77: 1u; C0402
C73, C75, C76, C102, C104, C107, C109: 0.1u; C0402
C103, C106, C108: 4.7u; C0402
C105, C110, C111: 0.022u; C0402
J2: HIROSE_FH19C-6S-0.5SH(10)
R4: 10k; R0402
R16: 5.1M; R0402
R53, R56, R59: 280R; R0402
R54, R57, R60: 13.7k; R0402
R55, R58, R61: 3.74k; R0402
TP14, TP15, TP16, TP17: TESTPOINT; TP_P76H50
U25: ADS7841E_2K5; DBQ16
U26, U28, U29: TLV9051IDCKR; SC70-5P65_210X110L36X22N_TLV9051

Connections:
!CS!_SUN_X+: U25.15 (!CS); also elsewhere on the board
+3V3: C72.1, C73.1, C74.1, C75.1, C76.1, C77.1, C103.1, C104.1, C106.1, C107.1, C108.1, C109.1, R4.2, R54.2, R57.2, R60.2, U25.1 (VCC+_2), U25.8 (VREF), U25.9 (VCC+), U26.5 (V+), U28.5 (V+), U29.5 (V+); also elsewhere on the board
GND: C72.2, C73.2, C74.2, C75.2, C76.2, C77.2, C102.2, C103.2, C104.2, C106.2, C107.2, C108.2, C109.2, J2.2, J2.4, J2.6, J2.7 (MTGTAB1), J2.8 (MTGTAB2), R16.1, R53.1, R56.1, R59.1, U25.6 (COM), U25.10 (GND), U25.11 (MODE), U26.2 (V-), U28.2 (V-), U29.2 (V-); also elsewhere on the board
unnamed: C102.1, R4.1, U25.7 (!SHDN)
unnamed: TP17.1, U25.2 (CH0)
unnamed: C105.1, J2.1, R55.1, U26.3 (-)
unnamed: R16.2, U25.13 (BUSY)
unnamed: R53.2, R54.1, U26.1 (+)
unnamed: C110.1, J2.3, R58.1, U28.3 (-)
unnamed: R56.2, R57.1, U28.1 (+)
unnamed: C111.1, J2.5, R61.1, U29.3 (-)
unnamed: R59.2, R60.1, U29.1 (+)
UCB0_SPI_CLK: U25.16 (DCLK); also elsewhere on the board
UCB0_SPI_MISO: U25.12 (DOUT); also elsewhere on the board
UCB0_SPI_MOSI: U25.14 (DIN); also elsewhere on the board
X+_0_DEGREES: C105.2, R55.2, TP14.1, U25.3 (CH1), U26.4 (OUT)
X+_120_DEGREES: C110.2, R58.2, TP15.1, U25.4 (CH2), U28.4 (OUT)
X+_240_DEGREES: C111.2, R61.2, TP16.1, U25.5 (CH3), U29.4 (OUT)

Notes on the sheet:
Thomas Christison

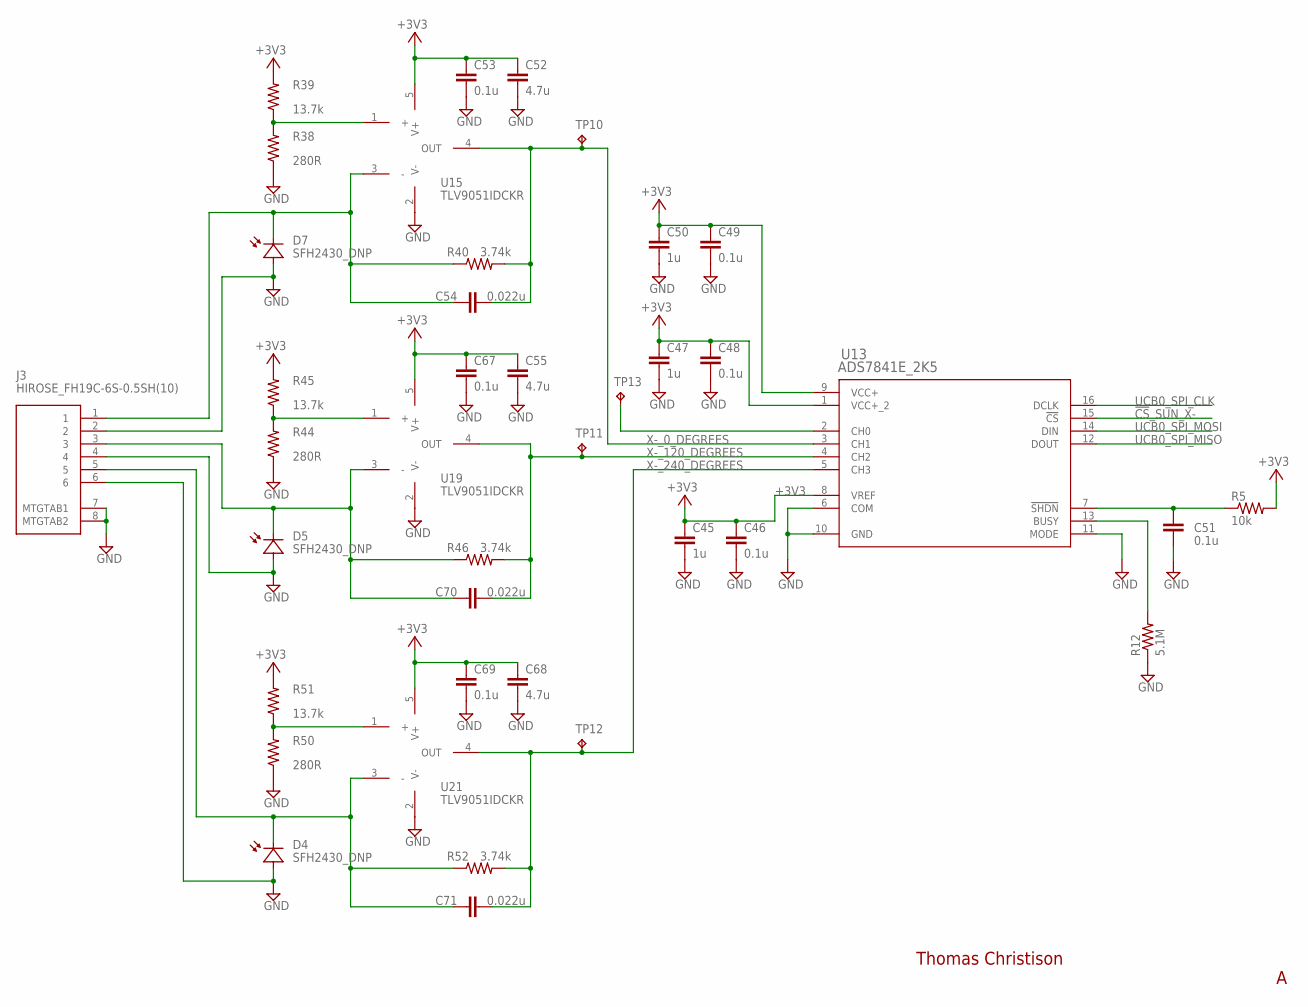
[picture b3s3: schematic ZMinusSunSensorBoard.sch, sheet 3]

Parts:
C45, C47, C50: 1u; C0402
C46, C48, C49, C51, C53, C67, C69: 0.1u; C0402
C52, C55, C68: 4.7u; C0402
C54, C70, C71: 0.022u; C0402
J3: HIROSE_FH19C-6S-0.5SH(10)
R5: 10k; R0402
R12: 5.1M; R0402
R38, R44, R50: 280R; R0402
R39, R45, R51: 13.7k; R0402
R40, R46, R52: 3.74k; R0402
TP10, TP11, TP12, TP13: TESTPOINT; TP_P76H50
U13: ADS7841E_2K5; DBQ16
U15, U19, U21: TLV9051IDCKR; SC70-5P65_210X110L36X22N_TLV9051

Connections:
!CS!_SUN_X-: U13.15 (!CS); also elsewhere on the board
+3V3: C45.1, C46.1, C47.1, C48.1, C49.1, C50.1, C52.1, C53.1, C55.1, C67.1, C68.1, C69.1, R5.2, R39.2, R45.2, R51.2, U13.1 (VCC+_2), U13.8 (VREF), U13.9 (VCC+), U15.5 (V+), U19.5 (V+), U21.5 (V+); also elsewhere on the board
GND: C45.2, C46.2, C47.2, C48.2, C49.2, C50.2, C51.2, C52.2, C53.2, C55.2, C67.2, C68.2, C69.2, J3.2, J3.4, J3.6, J3.7 (MTGTAB1), J3.8 (MTGTAB2), R12.1, R38.1, R44.1, R50.1, U13.6 (COM), U13.10 (GND), U13.11 (MODE), U15.2 (V-), U19.2 (V-), U21.2 (V-); also elsewhere on the board
unnamed: TP13.1, U13.2 (CH0)
unnamed: C51.1, R5.1, U13.7 (!SHDN)
unnamed: C54.1, J3.1, R40.1, U15.3 (-)
unnamed: R38.2, R39.1, U15.1 (+)
unnamed: C70.1, J3.3, R46.1, U19.3 (-)
unnamed: R44.2, R45.1, U19.1 (+)
unnamed: C71.1, J3.5, R52.1, U21.3 (-)
unnamed: R50.2, R51.1, U21.1 (+)
unnamed: R12.2, U13.13 (BUSY)
UCB0_SPI_CLK: U13.16 (DCLK); also elsewhere on the board
UCB0_SPI_MISO: U13.12 (DOUT); also elsewhere on the board
UCB0_SPI_MOSI: U13.14 (DIN); also elsewhere on the board
X-_0_DEGREES: C54.2, R40.2, TP10.1, U13.3 (CH1), U15.4 (OUT)
X-_120_DEGREES: C70.2, R46.2, TP11.1, U13.4 (CH2), U19.4 (OUT)
X-_240_DEGREES: C71.2, R52.2, TP12.1, U13.5 (CH3), U21.4 (OUT)

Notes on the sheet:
Thomas Christison
